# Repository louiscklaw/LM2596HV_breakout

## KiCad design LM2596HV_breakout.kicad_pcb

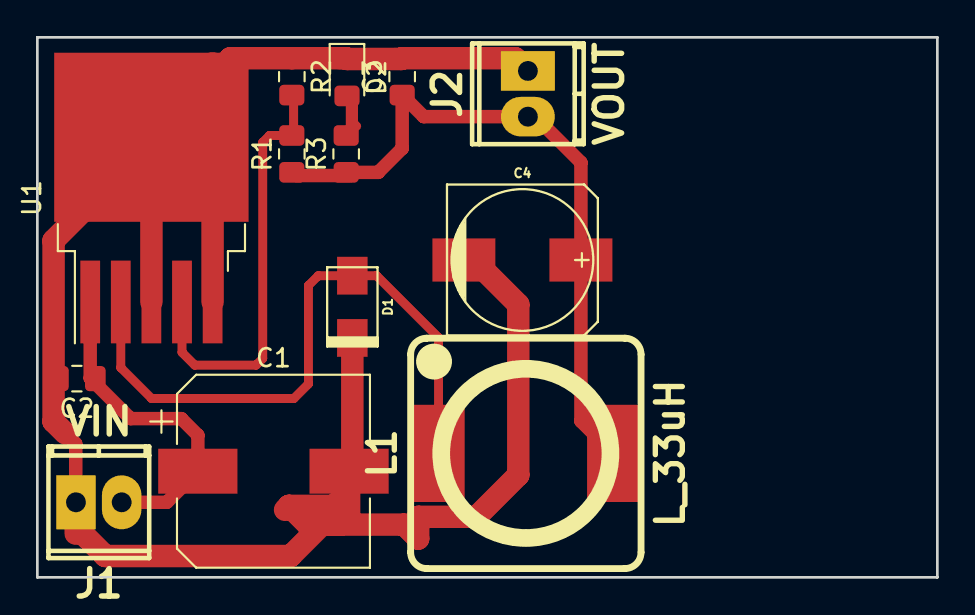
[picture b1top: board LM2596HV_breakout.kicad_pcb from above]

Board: 2 copper layers, 50.0 x 30.0 mm, 13 parts (0 on the bottom side), 6 nets.

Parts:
C1: CP100uf,63V; CP_Elec_10x10.5
C2, C3: C103; C_0805_2012Metric_Pad1.15x1.40mm_HandSolder
C4: CP220uf,35V; c_elec_8x10.5
D1: 1N5824; do214ac
D2: LED_GREEN; LED_0805_2012Metric_Pad1.15x1.40mm_HandSolder
J1: VIN; mpt_0,5%2f2-2,54
J2: VOUT; mpt_0,5%2f2-2,54
L1: L_33uH; inductor_smd_12.5x7.5mm
R1: RVAR; R_0805_2012Metric_Pad1.15x1.40mm_HandSolder
R2: R331; R_0805_2012Metric_Pad1.15x1.40mm_HandSolder
R3: R511; R_0805_2012Metric_Pad1.15x1.40mm_HandSolder
U1: LM2596HVS; TO-263-5_TabPin3

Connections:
GND: C1.2, C2.2, C3.2, C4.2, D1.2, D2.1, J1.1, J2.1, R2.1, U1.3, U1.5
unnamed: D1.1, L1.1, U1.2
unnamed: D2.2, R3.2
unnamed: R1.2, R2.2, U1.4
VIN: C1.1, C2.1, J1.2, U1.1
VOUT: C3.1, C4.1, J2.2, L1.2, R1.1, R3.1

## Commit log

2018-10-26 update,
2020-05-06 ci: init travis token,
2020-05-06 ci: init travis build config,
